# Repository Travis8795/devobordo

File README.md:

# devobordo

devobordo is a custom RP2040 development board designed from scratch in KiCad.

The goal of this project was try and work on the RP2040 architecture, power design, PCB layout, and manufacturability constraints (JLCPCB).

This board provides a minimal but fully functional RP2040 platform with clean power routing, proper decoupling, USB interface, full GPIO breakout for experimentation, and battery capability.

| front | back |
| :---: | :---: |
|  |  |

## Features

- RP2040 (Dual-core ARM Cortex-M0+ @ 133MHz)
- USB-C and battery power input
- MCP1700 3.3V linear regulator
- External QSPI Flash
- 12 MHz crystal oscillator
- SWD programming/debug header
- Dual LED indicators:
  - Power LED (3V3)
  - GPIO25 activity LED
- Full GPIO breakout headers
- 2-layer PCB optimized for low impedance power routing

## Power Architecture
*DO NOT CHARGE THE BATTERY WITH THE BOARD, CHARGE IT WITH AN EXTERNAL CHARGER*
- USB 5V input
- Reverse protection diode
- MCP1700 3.3V LDO regulator
- Wide 3V3 power backbone (low impedance design)
- Ground plane with via stitching
- Proper decoupling for:
  - 3V3 rail
  - 1V1 core regulator
  - QSPI flash
  - Crystal oscillator

## Designed With

- KiCad 9
- JLCPCB assembly constraints
- RP2040 datasheet reference design
- Blueprint Hackclub devboard guide

## Manufacturing

- 2-layer PCB
- 1oz copper
- JLCPCB assembly
- Standard component footprints (0603, 0402)

## What I Learned

- RP2040 power domain separation (3V3 vs 1V1)
- Decoupling capacitor placement strategy
- Thermal relief tuning
- USB differential routing basics
- DRC debugging
- Dealing with ground isolated islands

---

| front layer | back layer | schema |
| :---: | :---: | :---: |
|  |  |  |

## BOM table

| Description       | Value        | Footprint | LCSC Part # | Quantity | Notes             |
| ----------------- | ------------ | --------- | ----------- | -------- | ----------------- |
| Microcontroller   | RP2040       | QFN-56    | C2040       | 1        | Main MCU          |
| QSPI Flash        | W25Q16JV     | SOIC-8    | C97521      | 1        | External flash    |
| LDO Regulator     | MCP1700-3302 | SOT-23    | C62354      | 1        | 3.3V regulator    |
| Crystal           | 12MHz        | 3225      | C9002       | 1        | Main clock        |
| LED               | Red 0603     | 0603      | C2286       | 2        | Power indicator, and GPIO25|
| Resistor          | 1kΩ          | 0402      | C21190      | 2        | LED current limit |
| Resistor          | 27Ω         | 0402      | C21190      | 2        | USB D+/D- |
| Resistor          | 5.1KΩ         | 0402      | C21190      | 2        | CC pull down |
| Ceramic Capacitor | 100nF        | 0402      | C14663      | 11        | Decoupling        |
| Ceramic Capacitor | 10uF         | 0603      | C19702      | 2        | Bulk filtering    |
| Ceramic Capacitor | 1uF          | 0402      | C15849      | 2        | Core regulator    |
| Ceramic Capacitor | 33pF          | 0402      | C1562      | 2        | crystal filtering    |
| Push Button | SW_Push | SW_Push_SPST_NO_Alps_SKRK  | C341730      | 1        | Bootloder    |
| Diod | 1N4148WT | D_SOD-123  | C78089      | 2       | Reverse protection    |
| USB_C receptacle | USB_C_Receptacle_USB2.0_14P | USB_C_Receptacle_HRO_TYPE-C-31-M-12  | C165948      | 1        | USB connection    |

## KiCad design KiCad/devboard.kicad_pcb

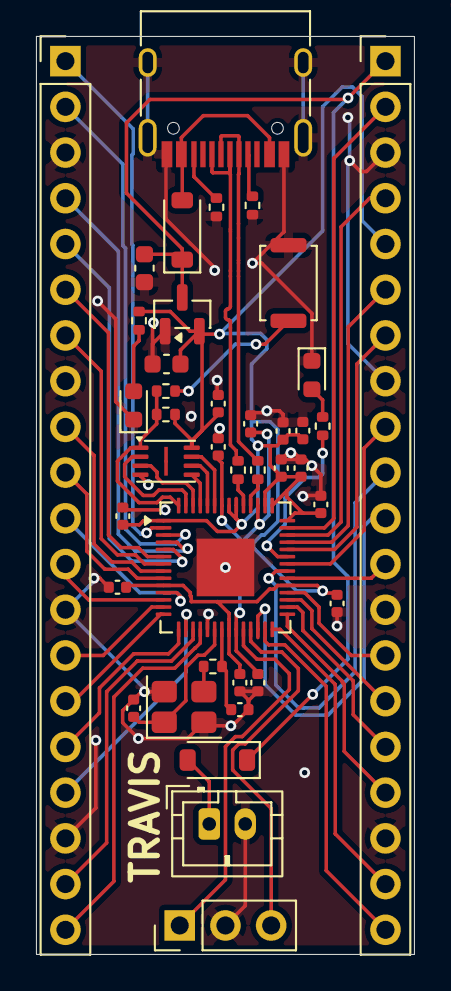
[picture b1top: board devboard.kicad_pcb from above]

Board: 2 copper layers, 21.0 x 51.0 mm, 40 parts (0 on the bottom side), 57 nets.

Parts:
C1, C2, C3, C4, C5, C6, C7, C8, C10, C11, C17: 0.1uF; C_0402_1005Metric
C9, C12: 1uF; C_0402_1005Metric
C13, C14: 10uF; C_0603_1608Metric
C15, C16: 33pF; C_0402_1005Metric
D1, D2: 1N4148WT; D_SOD-123
D3, D4: LED; LED_0603_1608Metric
J1: USB_C_Receptacle_USB2.0_14P; USB_C_Receptacle_HRO_TYPE-C-31-M-12
J2: Conn_01x02; JST_PH_B2B-PH-K_1x02_P2.00mm_Vertical
J3, J5: Conn_01x20; PinHeader_1x20_P2.54mm_Vertical
J4: Conn_01x03; PinHeader_1x03_P2.54mm_Vertical
R1, R2: 5.1K; R_0402_1005Metric
R3, R4: 27; R_0402_1005Metric
R5, R6, R8, R9: 1K; R_0402_1005Metric
R7: 10K; R_0402_1005Metric
SW1: SW_Push; SW_Push_SPST_NO_Alps_SKRK
U1: RP2040; QFN-56-1EP_7x7mm_P0.4mm_EP3.2x3.2mm
U2: MCP1700x-330xxTT; SOT-23
U3: W25Q16JVZPIQ TR; Winbond_USON-8-1EP_3x2mm_P0.5mm_EP0.2x1.6mm
Y1: 12 MHz; Crystal_SMD_3225-4Pin_3.2x2.5mm

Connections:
+1V1: C10.1, C11.1, C12.1, U1.23 (DVDD), U1.45 (VREG_VOUT), U1.50 (DVDD)
+3V3: C1.1, C2.1, C3.1, C4.1, C5.1, C6.1, C7.1, C8.1, C9.1, C14.1, C17.1, J5.5, R7.1, R8.1, U1.1 (IOVDD), U1.10 (IOVDD), U1.22 (IOVDD), U1.33 (IOVDD), U1.42 (IOVDD), U1.43 (ADC_AVDD), U1.44 (VREG_VIN), U1.48 (USB_VDD), U1.49 (IOVDD), U2.2 (VO), U3.8 (VCC)
GND: C1.2, C2.2, C3.2, C4.2, C5.2, C6.2, C7.2, C8.2, C9.2, C10.2, C11.2, C12.2, C13.2, C14.2, C15.1, C16.1, C17.2, D3.1 (K), D4.1 (K), J1.A1 (GND), J1.A12 (GND), J1.B1 (GND), J1.B12 (GND), J1.S1 (SHIELD), J2.2, J3.3, J3.8, J3.13, J3.18, J4.2, J5.3, J5.8, J5.13, J5.18, R1.2, R2.2, SW1.1, U1.19 (TESTEN), U1.57 (GND), U2.1 (GND), U3.4 (GND), Y1.2 (G), Y1.4 (G)
GPIO0: J3.1, U1.2 (GPIO0)
GPIO1: J3.2, U1.3 (GPIO1)
GPIO2: J3.4, U1.4 (GPIO2)
GPIO3: J3.5, U1.5 (GPIO3)
GPIO4: J3.6, U1.6 (GPIO4)
GPIO5: J3.7, U1.7 (GPIO5)
GPIO6: J3.9, U1.8 (GPIO6)
GPIO7: J3.10, U1.9 (GPIO7)
GPIO8: J3.11, U1.11 (GPIO8)
GPIO9: J3.12, U1.12 (GPIO9)
GPIO10: J3.14, U1.13 (GPIO10)
GPIO11: J3.15, U1.14 (GPIO11)
GPIO12: J3.16, U1.15 (GPIO12)
GPIO13: J3.17, U1.16 (GPIO13)
GPIO14: J3.19, U1.17 (GPIO14)
GPIO15: J3.20, U1.18 (GPIO15)
GPIO16: J5.20, U1.27 (GPIO16)
GPIO17: J5.19, U1.28 (GPIO17)
GPIO18: J5.17, U1.29 (GPIO18)
GPIO19: J5.16, U1.30 (GPIO19)
GPIO20: J5.15, U1.31 (GPIO20)
GPIO21: J5.14, U1.32 (GPIO21)
GPIO22: J5.12, U1.34 (GPIO22)
GPIO23: J5.10, U1.35 (GPIO23)
GPIO24: J5.9, U1.36 (GPIO24)
GPIO25: R9.1, U1.37 (GPIO25)
GPIO26/ADC0: J5.7, U1.38 (GPIO26/ADC0)
GPIO27/ADC1: J5.6, U1.39 (GPIO27/ADC1)
GPIO28/ADC2: J5.4, U1.40 (GPIO28/ADC2)
GPIO29/ADC3: J5.2, U1.41 (GPIO29/ADC3)
unnamed: D1.2 (A), J1.A4 (VBUS), J1.A9 (VBUS), J1.B4 (VBUS), J1.B9 (VBUS)
unnamed: D2.2 (A), J2.1
unnamed: D3.2 (A), R8.2
unnamed: D4.2 (A), R9.2
unnamed: J1.A5 (CC1), R1.1
unnamed: J1.B5 (CC2), R2.1
unnamed: R5.1, Y1.3
unnamed: R6.1, SW1.2
unnamed: R3.2, U1.46 (USB_DM)
unnamed: R4.2, U1.47 (USB_DP)
QSPI_SCLK: U1.52 (QSPI_SCLK), U3.6 (CLK)
QSPI_SD0: U1.53 (QSPI_SD0), U3.5 (DI/IO_{0})
QSPI_SD1: U1.55 (QSPI_SD1), U3.2 (DO/IO_{1})
QSPI_SD2: U1.54 (QSPI_SD2), U3.3 (~WP/IO_{2})
QSPI_SD3: U1.51 (QSPI_SD3), U3.7 (~HOLD/~RESET/IO_{3})
QSPI_SS: R6.2, R7.2, U1.56 (~QSPI_SS), U3.1 (~CS)
RUN: J5.11, U1.26 (RUN)
SWCLK: J4.1, U1.24 (SWCLK)
SWDIO: J4.3, U1.25 (SWDIO)
USB_D+: J1.A6 (D+), J1.B6 (D+), R4.1
USB_D-: J1.A7 (D-), J1.B7 (D-), R3.1
VBUS: C13.1, D1.1 (K), D2.1 (K), J5.1, U2.3 (VI)
XIN: C15.2, U1.20 (XIN), Y1.1
XOUT: C16.2, R5.2, U1.21 (XOUT)

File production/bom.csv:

Designator,Footprint,Quantity,Value,LCSC Part #
"C1, C10, C11, C17, C2, C3, C4, C5, C6, C7, C8",0402,11,0.1uF,
"C12, C9",0402,2,1uF,
"C13, C14",0603,2,10uF,
"C15, C16",0402,2,33pF,
"D1, D2",D_SOD-123,2,1N4148WT,
"D3, D4",0603,2,LED,
J1,USB_C_Receptacle_HRO_TYPE-C-31-M-12,1,USB_C_Receptacle_USB2.0_14P,
J2,JST_PH_B2B-PH-K_1x02_P2.00mm_Vertical,1,Conn_01x02,
"J3, J5",PinHeader_1x20_P2.54mm_Vertical,2,Conn_01x20,
J4,PinHeader_1x03_P2.54mm_Vertical,1,Conn_01x03,
"R1, R2",0402,2,5.1K,
"R3, R4",0402,2,27,
"R5, R6, R8, R9",0402,4,1K,
R7,0402,1,10K,
SW1,SW_Push_SPST_NO_Alps_SKRK,1,SW_Push,
U1,QFN-56-1EP_7x7mm_P0.4mm_EP3.2x3.2mm,1,RP2040,
U2,SOT-23,1,MCP1700x-330xxTT,
U3,Winbond_USON-8-1EP_3x2mm_P0.5mm_EP0.2x1.6mm,1,W25Q16JVZPIQ TR,
Y1,Crystal_SMD_3225-4Pin_3.2x2.5mm,1,12 MHz,

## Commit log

2026-02-10 Enhance README with project details and features
    Expanded the README to include detailed features, power architecture, PCB design goals, manufacturing details, and lessons learned from the project.
2026-02-10 Revise README for better project documentation
    Updated README.md to improve project clarity and organization.
2026-02-10 Update README with board images and schema
    Added images of the front and back layers of the board along with their schema.
2026-02-10 Revise README with project goals and design updates
    Updated project goals and added battery capability to the board description. Revised PCB design goals and added additional design considerations.
2026-02-10 Update README with component details
    Added component descriptions and specifications to the README.
2026-02-10 Revise parts list in README.md
    Updated component specifications and added new components in the parts list.
2026-02-10 Fix title formatting in README.md
    Updated project title formatting in README.
2026-02-18 reorganizing files
2026-03-09 Add README with board compatibility and GPIO info
2026-03-09 Update README with link to latest MicroPython update
    Add link to latest MicroPython update for RPI PICO.
2026-03-23 Add battery charging warning to README
    Added warning about charging the battery with the board.
